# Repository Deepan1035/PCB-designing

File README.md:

View this project on [CADLAB.io](https://cadlab.io/project/29139). 

# PCB-designing

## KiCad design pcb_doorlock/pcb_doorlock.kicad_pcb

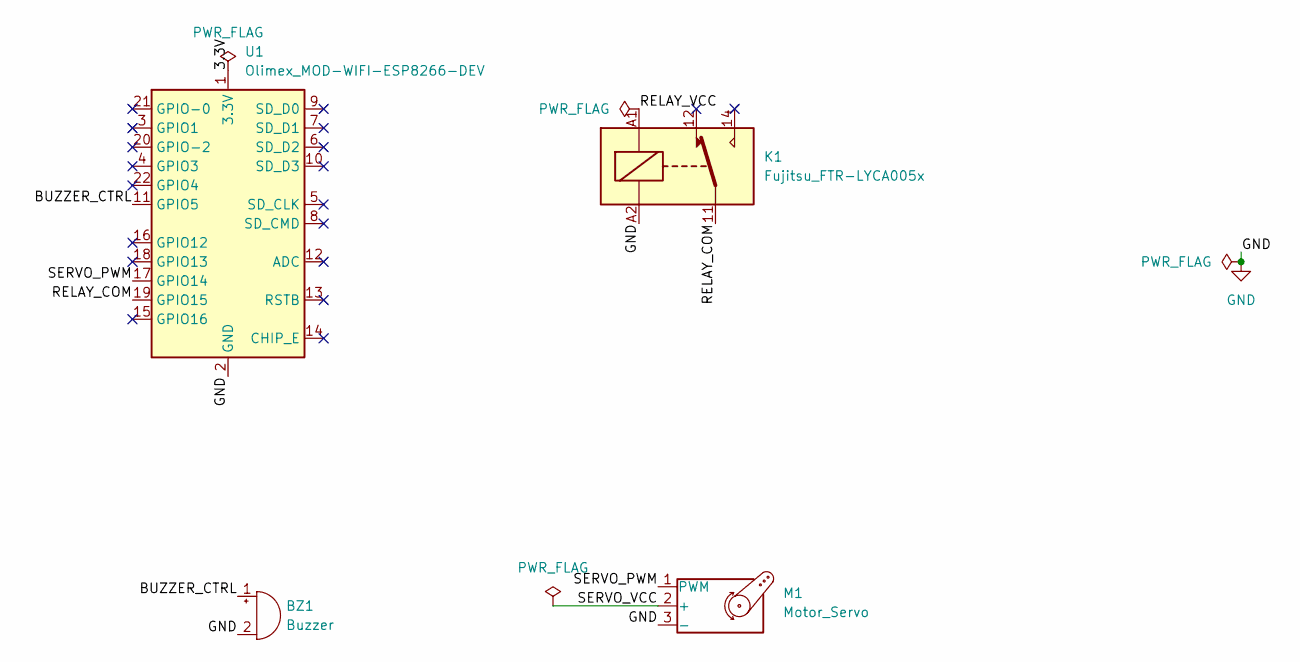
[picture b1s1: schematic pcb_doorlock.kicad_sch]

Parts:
BZ1: Buzzer; Buzzer_12x9.5RM7.6
K1: Fujitsu_FTR-LYCA005x; Relay_SPDT_Fujitsu_FTR-LYCA005x_FormC_Vertical
M1: Motor_Servo; PinHeader_1x03_P2.54mm_Vertical_SMD_Pin1Left
U1: Olimex_MOD-WIFI-ESP8266-DEV

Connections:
/3.3V: U1.1 (3.3V)
/BUZZER_CTRL: BZ1.1 (+), U1.11 (GPIO5)
/RELAY_COM: K1.11, U1.19 (GPIO15)
/RELAY_VCC: K1.A1
/SERVO_PWM: M1.1 (PWM), U1.17 (GPIO14)
/SERVO_VCC: M1.2 (+)
GND: BZ1.2 (-), K1.A2, M1.3 (-), U1.2 (GND)

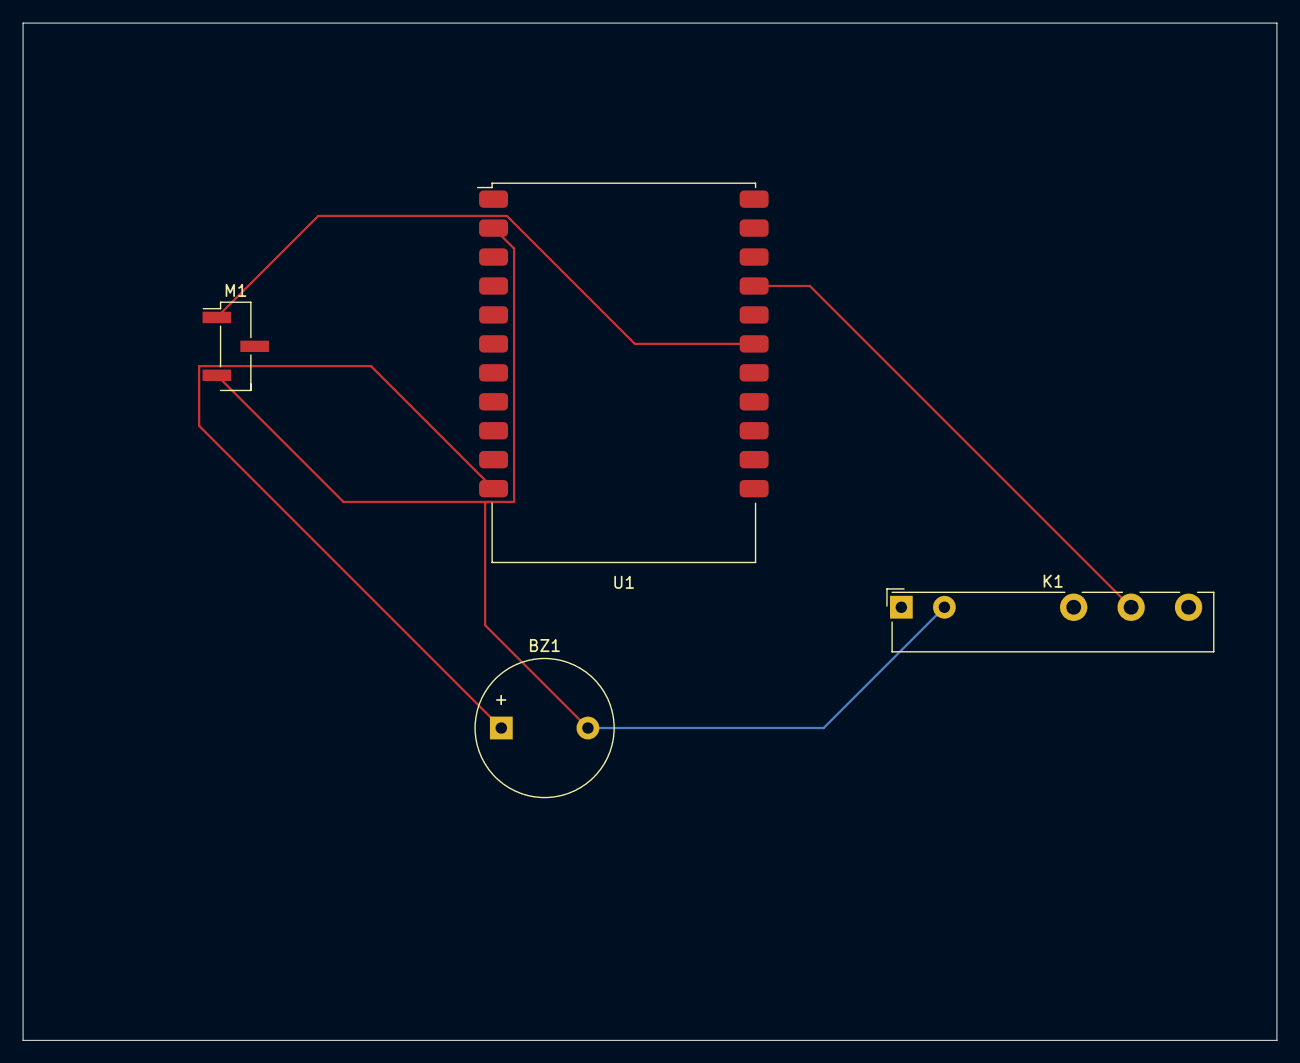
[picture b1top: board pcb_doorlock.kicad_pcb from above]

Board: 2 copper layers, 110.0 x 89.2 mm, 4 parts (0 on the bottom side), 4 nets.

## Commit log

2025-03-24 PCB design
2025-04-02 door lock done
2025-04-02 Backlink to CADLAB.io has been added.
